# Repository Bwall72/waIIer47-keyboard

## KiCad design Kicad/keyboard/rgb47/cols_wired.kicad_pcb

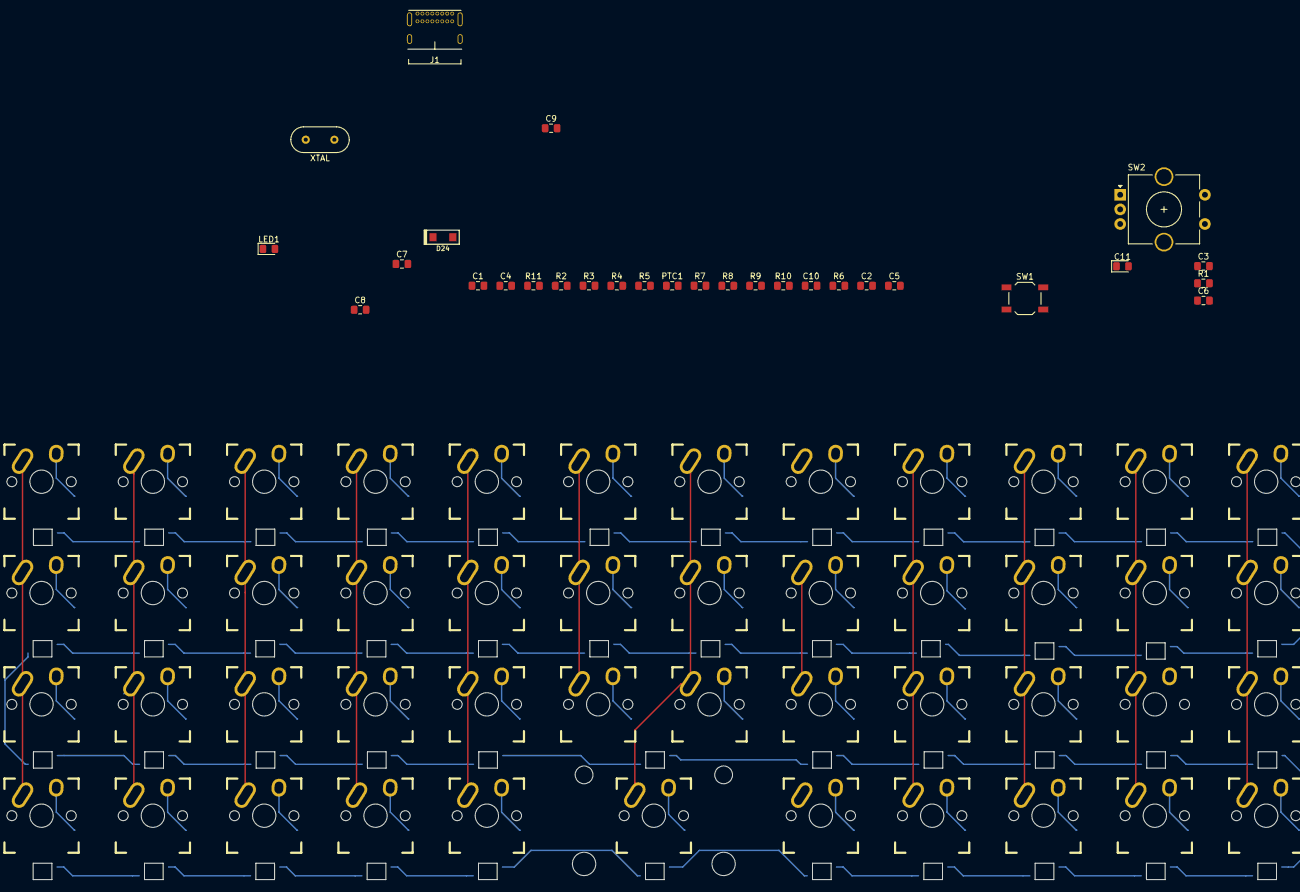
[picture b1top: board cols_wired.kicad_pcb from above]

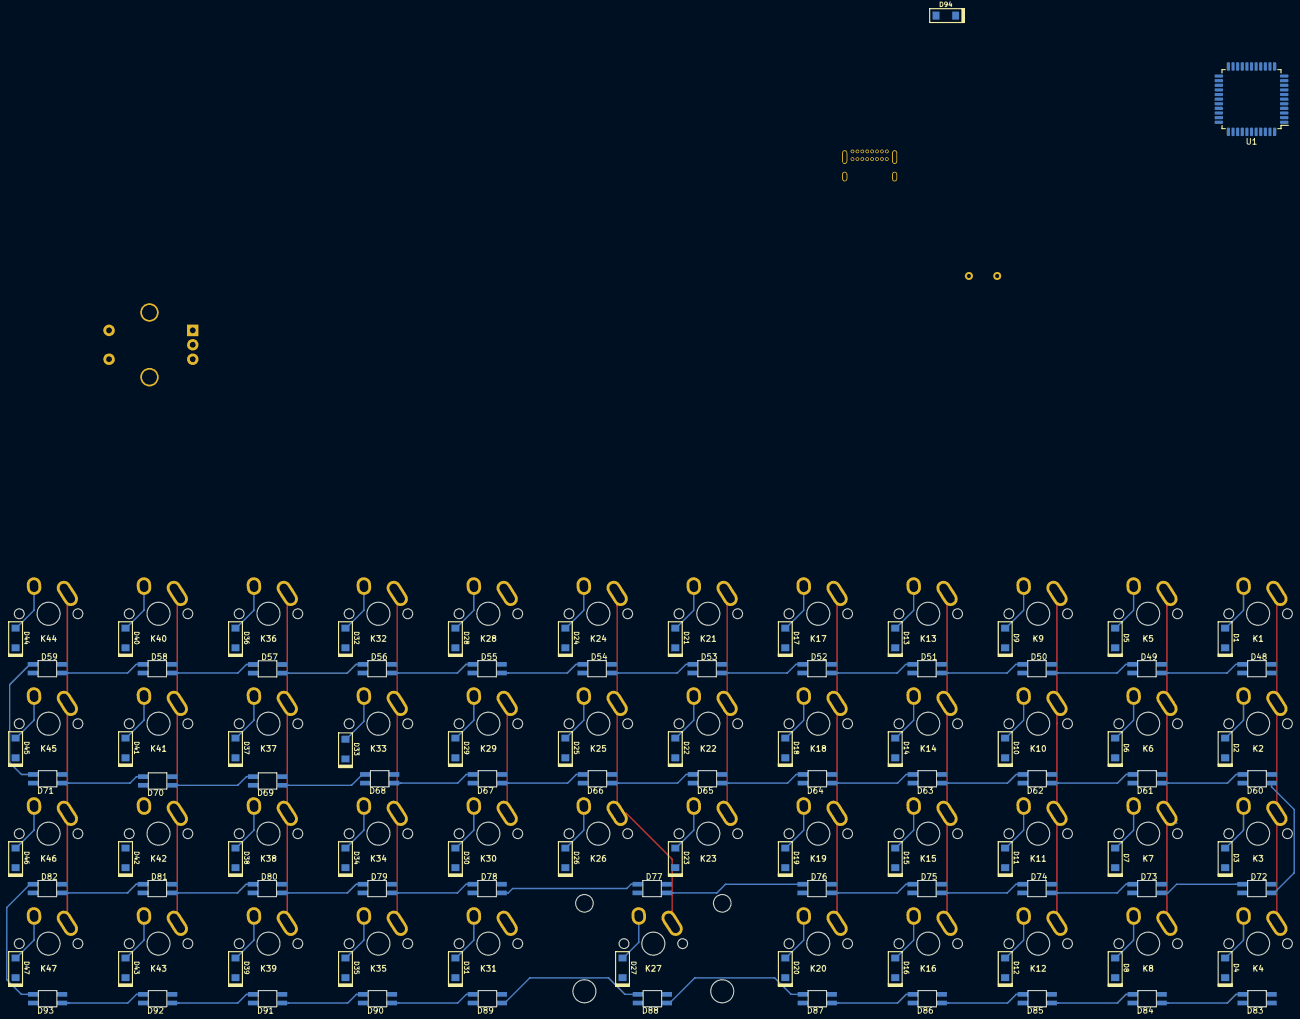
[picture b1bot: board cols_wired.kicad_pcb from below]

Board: 2 copper layers, 171 parts (49 on the bottom side), 127 nets.

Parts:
C1, C2: 22p; C_0805_2012Metric_Pad1.15x1.40mm_HandSolder
C3, C4, C5, C6, C7, C8, C9, C10: 0.1u; C_0805_2012Metric_Pad1.15x1.40mm_HandSolder
C11: 1u; D_0805_2012Metric_Pad1.15x1.40mm_HandSolder
D1, D2, D3, D4, D5, D6, D7, D8, D9, D10, D11, D12, D13, D14, D15, D16, D17, D18, D19, D20, D21, D22, D23, D24, D24#2, D25, D26, D27, D28, D29, D30, D31, D32, D33, D34, D35, D36, D37, D38, D39, D40, D41, D42, D43, D44, D45, D46, D47, D94: D; D_SOD123
D48, D49, D50, D51, D52, D53, D54, D55, D56, D57, D58, D59, D60, D61, D62, D63, D64, D65, D66, D67, D68, D69, D70, D71, D72, D73, D74, D75, D76, D77, D78, D79, D80, D81, D82, D83, D84, D85, D86, D87, D88, D89, D90, D91, D92, D93: SK6812; sk6812_mini_E_cuts
J1: USB_C_Receptacle_USB2.0; USB_C_GCT_USB4085
K1, K2, K3, K4, K5, K6, K7, K8, K9, K10, K11, K12, K13, K14, K15, K16, K17, K18, K19, K20, K21, K22, K23, K24, K25, K26, K28, K29, K30, K31, K32, K33, K34, K35, K36, K37, K38, K39, K40, K41, K42, K43, K44, K45, K46, K47: KEYSW; Mx_Alps_100
K27: KEYSW; Mx_Alps_200
LED1: LED; LED_0805_2012Metric_Pad1.15x1.40mm_HandSolder
PTC1: PTC 1.5A; Fuse_0805_2012Metric_Pad1.15x1.40mm_HandSolder
R1, R6, R7, R8, R9, R11: 10k; R_0805_2012Metric_Pad1.15x1.40mm_HandSolder
R2, R3: 5.1k; R_0805_2012Metric_Pad1.15x1.40mm_HandSolder
R4, R5: 22; R_0805_2012Metric_Pad1.15x1.40mm_HandSolder
R10: 220; R_0805_2012Metric_Pad1.15x1.40mm_HandSolder
SW1: SW_PUSH; SW_SPST_TL3342
SW2: Rotary_Encoder_Switch; RotaryEncoder_Alps_EC11E-Switch_Vertical_H20mm_CircularMoun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
U1: ATMEGA32U4; LQFP-44_10x10mm_P0.8mm
X1: XTAL; XTAL_HC_49_TH

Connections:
5V: C4.2, C6.2, C7.2, C8.2, C9.2, C10.2, D48.3, D49.3, D50.3, D51.3, D52.3, D53.3, D54.3, D55.3, D56.3, D57.3, D58.3, D59.3, D60.3, D61.3, D62.3, D63.3, D64.3, D65.3, D66.3, D67.3, D68.3, D69.3, D70.3, D71.3, D72.3, D73.3, D74.3, D75.3, D76.3, D77.3, D78.3, D79.3, D80.3, D81.3, D82.3, D83.3, D84.3, D85.3, D86.3, D87.3, D88.3, D89.3, D90.3, D91.3, D92.3, D93.3, PTC1.2, R1.1, R6.2, R8.2, R10.1, U1.2, U1.7, U1.14, U1.24, U1.34, U1.44
/COL0: K1.1, K2.1, K3.1, K4.1, U1.41
/COL1: K5.1, K6.1, K7.1, K8.1, U1.40
/COL2: K9.1, K10.1, K11.1, K12.1, U1.39
/COL3: K13.1, K14.1, K15.1, K16.1, U1.38
/COL4: K17.1, K18.1, K19.1, K20.1, U1.37
/COL5: K21.1, K22.1, K23.1, SW2.S2, U1.36
/COL6: K24.1, K25.1, K26.1, K27.1, U1.32
/COL7: K28.1, K29.1, K30.1, K31.1, U1.31
/COL8: K32.1, K33.1, K34.1, K35.1, U1.30
/COL9: K36.1, K37.1, K38.1, K39.1, U1.29
/COL10: K40.1, K41.1, K42.1, K43.1, U1.28
/COL11: K44.1, K45.1, K46.1, K47.1, U1.27
/D+: R5.1, U1.4
/D-: R4.1, U1.3
/ENCODER_A: R8.1, R9.2, SW2.A
/ENCODER_AOUT: C5.2, R9.1, U1.18
/ENCODER_B: R6.1, R7.2, SW2.B
/ENCODER_BOUT: C3.2, R7.1, U1.19
/ENCODER_S1: D24#2.2, D94.2, SW2.S1
/RESET: R1.2, SW1.1, U1.13
/RGB: D48.2, U1.25
/ROW0: D1.1, D5.1, D9.1, D13.1, D17.1, D21.1, D24.1, D28.1, D32.1, D36.1, D40.1, D44.1, D45.2, K45.2, U1.8
/ROW1: D2.1, D6.1, D10.1, D14.1, D18.1, D22.1, D25.1, D29.1, D33.1, D37.1, D41.1, D45.1, U1.9
/ROW2: D3.1, D7.1, D11.1, D15.1, D19.1, D23.1, D26.1, D30.1, D34.1, D38.1, D42.1, D46.1, D47.2, K47.2, U1.10
/ROW3: D4.1, D8.1, D12.1, D16.1, D20.1, D24#2.1, D27.1, D31.1, D35.1, D39.1, D43.1, D47.1, D94.1, U1.11
/XTAL1: C2.2, U1.16, X1.2
/XTAL2: C1.2, U1.17, X1.1
GND: C1.1, C2.1, C3.1, C4.1, C5.1, C6.1, C7.1, C8.1, C9.1, C10.1, C11.2, D48.1, D49.1, D50.1, D51.1, D52.1, D53.1, D54.1, D55.1, D56.1, D57.1, D58.1, D59.1, D60.1, D61.1, D62.1, D63.1, D64.1, D65.1, D66.1, D67.1, D68.1, D69.1, D70.1, D71.1, D72.1, D73.1, D74.1, D75.1, D76.1, D77.1, D78.1, D79.1, D80.1, D81.1, D82.1, D83.1, D84.1, D85.1, D86.1, D87.1, D88.1, D89.1, D90.1, D91.1, D92.1, D93.1, J1.A1, J1.A12, J1.B1, J1.B12, J1.S1, R2.1, R3.1, R11.1, SW1.2, U1.5, U1.15, U1.23, U1.35, U1.43
unnamed: C11.1, U1.6
unnamed: D1.2, K1.2
unnamed: D2.2, K2.2
unnamed: D3.2, K3.2
unnamed: D4.2, K4.2
unnamed: D5.2, K5.2
unnamed: D6.2, K6.2
unnamed: D7.2, K7.2
unnamed: D8.2, K8.2
unnamed: D9.2, K9.2
unnamed: D10.2, K10.2
unnamed: D11.2, K11.2
unnamed: D12.2, K12.2
unnamed: D13.2, K13.2
unnamed: D14.2, K14.2
unnamed: D15.2, K15.2
unnamed: D16.2, K16.2
unnamed: D17.2, K17.2
unnamed: D18.2, K18.2
unnamed: D19.2, K19.2
unnamed: D20.2, K20.2
unnamed: D21.2, K21.2
unnamed: D22.2, K22.2
unnamed: D23.2, K23.2
unnamed: D24.2, K24.2
unnamed: D25.2, K25.2
unnamed: D26.2, K26.2
unnamed: D27.2, K27.2
unnamed: D28.2, K28.2
unnamed: D29.2, K29.2
unnamed: D30.2, K30.2
unnamed: D31.2, K31.2
unnamed: D32.2, K32.2
unnamed: D33.2, K33.2
unnamed: D34.2, K34.2
unnamed: D35.2, K35.2
unnamed: D36.2, K36.2
unnamed: D37.2, K37.2
unnamed: D38.2, K38.2
unnamed: D39.2, K39.2
unnamed: D40.2, K40.2
unnamed: D41.2, K41.2
unnamed: D42.2, K42.2
unnamed: D43.2, K43.2
unnamed: D44.2, K44.2
unnamed: D46.2, K46.2
unnamed: D48.4, D49.2
unnamed: D49.4, D50.2
unnamed: D50.4, D51.2
unnamed: D51.4, D52.2
unnamed: D52.4, D53.2
unnamed: D53.4, D54.2
unnamed: D54.4, D55.2
unnamed: D55.4, D56.2
unnamed: D56.4, D57.2
unnamed: D57.4, D58.2
unnamed: D58.4, D59.2
unnamed: D59.4, D71.2
unnamed: D60.2, D61.4
unnamed: D60.4, D72.2
unnamed: D61.2, D62.4
unnamed: D62.2, D63.4
unnamed: D63.2, D64.4
unnamed: D64.2, D65.4
unnamed: D65.2, D66.4
unnamed: D66.2, D67.4
unnamed: D67.2, D68.4
unnamed: D68.2, D69.4
unnamed: D69.2, D70.4
unnamed: D70.2, D71.4
unnamed: D72.4, D73.2
unnamed: D73.4, D74.2
unnamed: D74.4, D75.2
unnamed: D75.4, D76.2
unnamed: D76.4, D77.2
unnamed: D77.4, D78.2
unnamed: D78.4, D79.2
unnamed: D79.4, D80.2
unnamed: D80.4, D81.2
unnamed: D81.4, D82.2
unnamed: D82.4, D93.2
unnamed: D83.2, D84.4
unnamed: D84.2, D85.4
unnamed: D85.2, D86.4
unnamed: D86.2, D87.4
unnamed: D87.2, D88.4
unnamed: D88.2, D89.4
unnamed: D89.2, D90.4
unnamed: D90.2, D91.4
unnamed: D91.2, D92.4
unnamed: D92.2, D93.4
unnamed: J1.A5, R2.2
unnamed: J1.A6, J1.B6, R5.2
unnamed: J1.A7, J1.B7, R4.2
unnamed: J1.B5, R3.2
unnamed: LED1.2, R10.2
unnamed: R11.2, U1.33
VCC: J1.A4, J1.A9, J1.B4, J1.B9, PTC1.1
